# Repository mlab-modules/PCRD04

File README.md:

<!--- PrjInfo ---> <!--- Please remove this line after manually editing --->
<!--- 00a56be08b96043df9e37d6aff7b6990 --->
<!--- Created:2019-02-18 14:38:16.708695: --->
<!--- Author:: --->
<!--- AuthorEmail:: --->
<!--- Tags:: --->
<!--- Ust:: --->
<!--- Label --->
<!--- ELabel --->
<!--- Name:PCRD04B: --->
# PCRD04B - Solid state cosmic radiation detector 
<!--- LongName --->
##
<!--- ELongName --->

<!--- Lead --->

<!--- ELead --->

<!--- Description --->
<!--- EDescription --->
<!--- Content --->
<!--- EContent --->
<sub><sup> Generated with [MLABweb](https://github.com/MLAB-project/MLABweb). (2019-02-18)</sup></sub>

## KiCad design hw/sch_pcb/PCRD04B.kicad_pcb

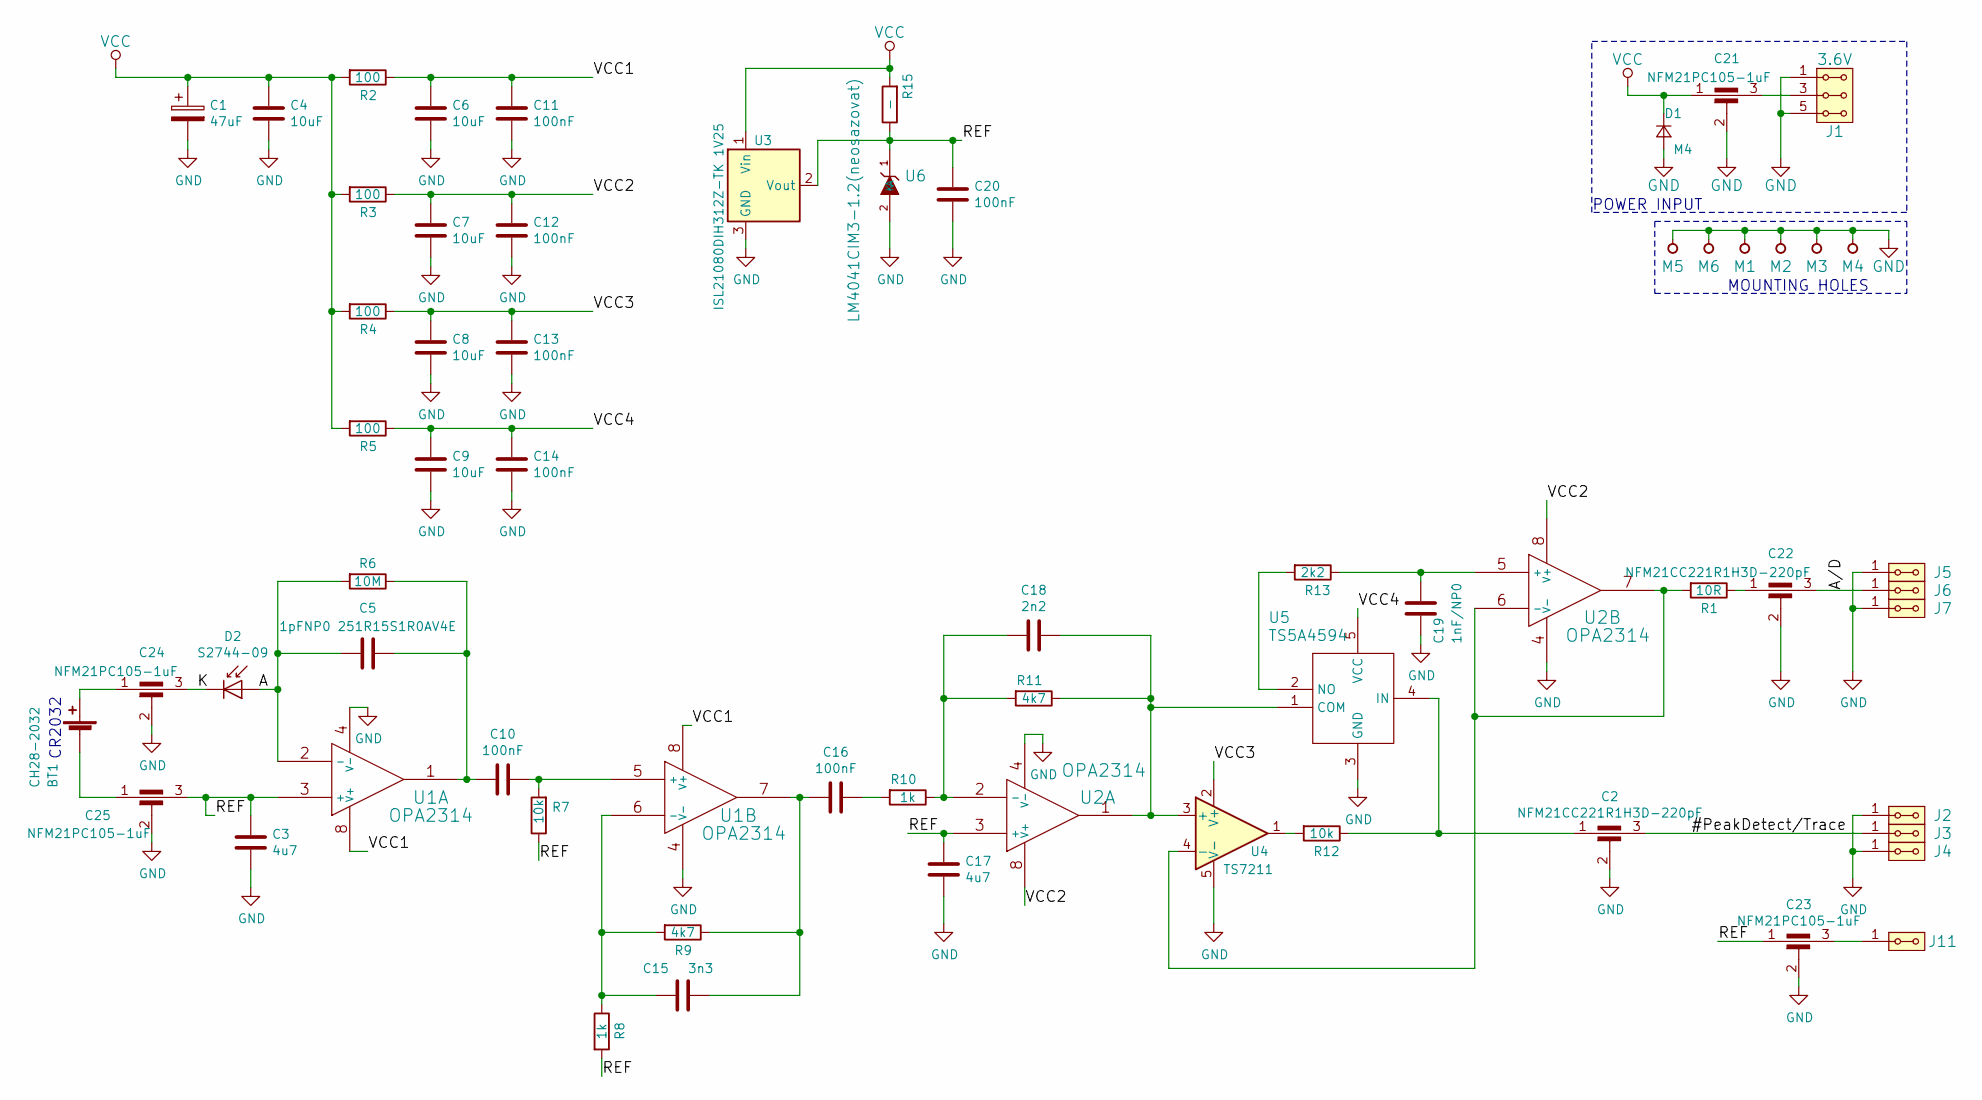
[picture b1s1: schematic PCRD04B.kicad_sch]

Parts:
BT1: CH28-2032
C1: 47uF; TantalC_SizeC_Reflow
C2, C22: NFM21CC221R1H3D-220pF; FIR1
C3, C17: 4u7; SMD-0805
C4, C6, C7, C8, C9: 10uF; SMD-0805
C5: 1pFNP0 251R15S1R0AV4E; SMD-0805
C10, C11, C12, C13, C14, C16, C20: 100nF; SMD-0805
C15: 3n3; SMD-0805
C18: 2n2; SMD-0805
C19: 1nF/NP0; SMD-0805
C21, C23, C24, C25: NFM21PC105-1uF; FIR1
D1: M4; Diode-SMA_Standard
D2: S2744-09; HAMAMATSU_S2744-09_rozs
J1: 3.6V; Straight_2x03
J2, J3, J4, J5, J6, J7, J11: HEADER_2x01_PARALLEL; Straight_2x01
M1, M2, M3, M4: HOLE; MountingHole_3mm
M5: BMIS-209-C
M6: BMI-S-210-F
R1: 10R; SMD-0805
R2, R3, R4, R5: 100; SMD-0805
R6: 10M; SMD-0805
R7, R12: 10k; SMD-0805
R8, R10: 1k; SMD-0805
R9, R11: 4k7; SMD-0805
R13: 2k2; SMD-0805
R15: -; SMD-0805
U1, U2: OPA2314; SOIC-8_3.9x4.9mm_Pitch1.27mm
U3: ISL21080DIH312Z-TK 1V25; SOT-23
U4: TS7211; SOT-23-5_HandSoldering
U5: TS5A4594; SOT-23-5_HandSoldering
U6: LM4041CIM3-1.2(neosazovat); SOT-23

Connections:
/#PeakDetect/Trace: C2.3, J3.1, J3.2
/A: C5.2, D2.2 (A), R6.2, U1.2 (-)
/A/D: C22.3, J6.1, J6.2
/K: C24.3, D2.1 (K)
/REF: C3.1, C17.1, C20.1, C23.1, C25.3, R7.1, R8.2, R15.1, U1.3 (+), U2.3 (+), U3.2 (Vout), U6.1 (K)
/VCC1: C6.1, C11.1, R2.1, U1.8 (V+)
/VCC2: C7.1, C12.1, R3.1, U2.8 (V+)
/VCC3: C8.1, C13.1, R4.1, U4.2 (V+)
/VCC4: C9.1, C14.1, R5.1, U5.5 (VCC)
GND: C1.2, C2.2, C3.2, C4.2, C6.2, C7.2, C8.2, C9.2, C11.2, C12.2, C13.2, C14.2, C17.2, C19.2, C20.2, C21.2, C22.2, C23.2, C24.2, C25.2, D1.2 (A), J1.1, J1.2, J1.5, J1.6, J2.1, J2.2, J4.1, J4.2, J5.1, J5.2, J7.1, J7.2, M1.1, M2.1, M3.1, M4.1, M5.1, M6.1, U1.4 (V-), U2.4 (V-), U3.3 (GND), U4.5 (V-), U5.3 (GND), U6.2 (A)
unnamed: BT1.1 (+), C24.1
unnamed: BT1.2 (-), C25.1
unnamed: C2.1, R12.1, U5.4 (IN)
unnamed: C10.1, R7.2, U1.5 (+)
unnamed: C5.1, C10.2, R6.1, U1.1
unnamed: C15.1, C16.2, R9.1, U1.7
unnamed: C15.2, R8.1, R9.2, U1.6 (-)
unnamed: C16.1, R10.2
unnamed: C18.1, R11.1, U2.1, U4.3 (+), U5.1 (COM)
unnamed: C18.2, R10.1, R11.2, U2.2 (-)
unnamed: C19.1, R13.1, U2.5 (+)
unnamed: C21.3, J1.3, J1.4
unnamed: C22.1, R1.1
unnamed: C23.3, J11.1, J11.2
unnamed: R1.2, U2.6 (-), U2.7, U4.4 (-)
unnamed: R12.2, U4.1
unnamed: R13.2, U5.2 (NO)
VCC: C1.1, C4.1, C21.1, D1.1 (K), R2.2, R3.2, R4.2, R5.2, R15.2, U3.1 (Vin)

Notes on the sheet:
CR2032
POWER INPUT
MOUNTING HOLES

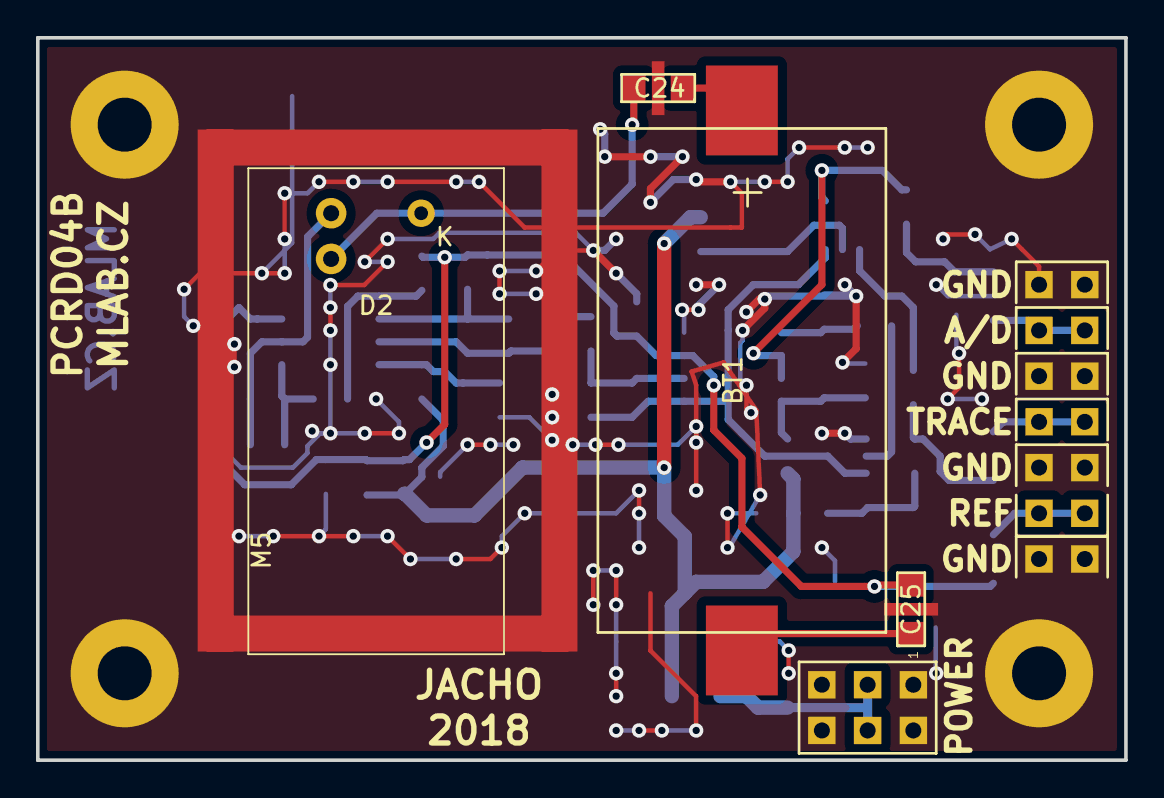
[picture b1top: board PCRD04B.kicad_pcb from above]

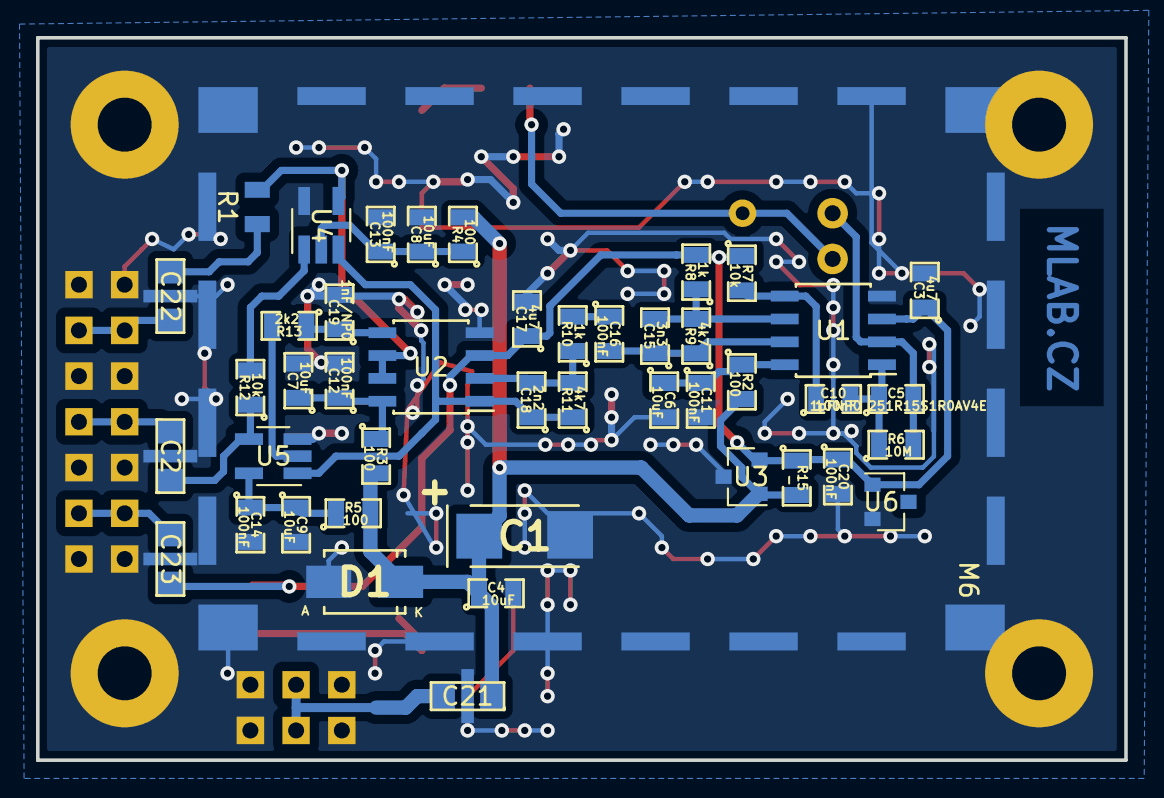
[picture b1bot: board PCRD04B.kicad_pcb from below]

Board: 2 copper layers, 60.5 x 40.1 mm, 62 parts (45 on the bottom side), 28 nets.

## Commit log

2018-07-01 [MLABweb] Documentaion edits; PCRD04A
2018-07-01 Edit
2018-08-04 [MLABweb] Documentaion edits; PCRD04B
2018-08-05 Editace modulu
2018-08-14 Novy .csv
2020-11-04 Fix license
2020-11-04 3D model
2020-11-04 Include renders in readme.
2021-04-14 Add workflow for automatic data preparation.
2022-04-06 automated commit; add github actions
2022-04-06 Update actions products
2022-04-06 clean and update templates
2023-02-14 update actions
2023-02-14 Update metadata files
2023-05-25 Update workflow files
2023-09-16 Update image to image_title
2023-09-16 Update status
